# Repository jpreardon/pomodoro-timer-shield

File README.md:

Pomodoro Timer Shield for Arduino
=================================

This is a Pomodoro Timer, implemented  as an Arduino shield. The source code, schematic and board layout (in Eagle) are all included in this repository. For more information about the project, visit http://jpreardon.com/projects/pomodoro-timer/

© Copyright 2012-2019 John P. Reardon
Licensed under the MIT license.

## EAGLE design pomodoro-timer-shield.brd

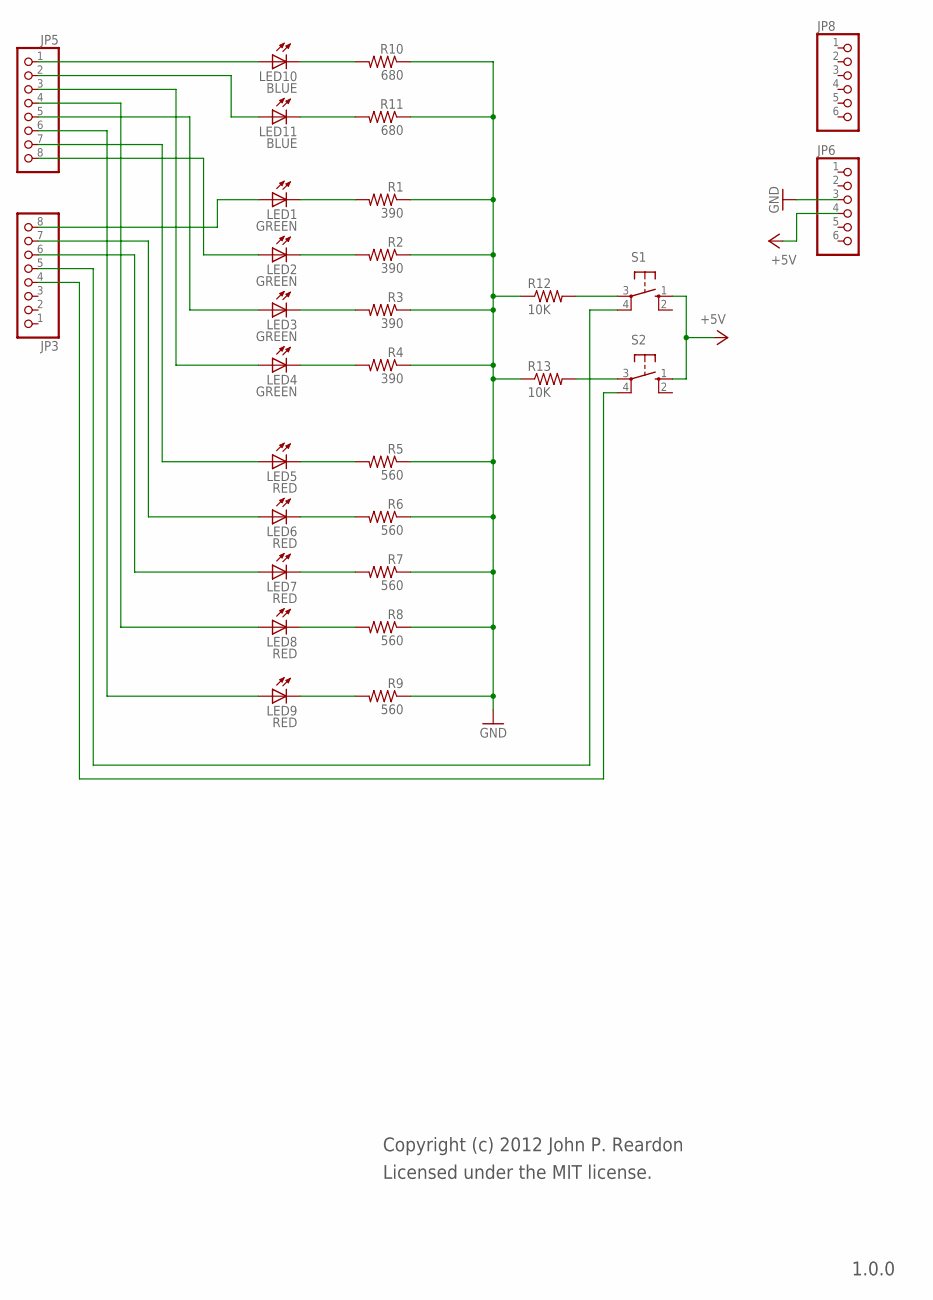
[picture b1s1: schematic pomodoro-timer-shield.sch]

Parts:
JP3, JP5: PINHD-1X8CLEANBIG; 1X08-CLEANBIG
JP6, JP8: PINHD-1X6CB; 1X06-CLEANBIG
LED1, LED2, LED3, LED4: GREEN; LED3MM
LED5, LED6, LED7, LED8, LED9: RED; LED3MM
LED10, LED11: BLUE; LED3MM
R1, R2, R3, R4: 390; 0204/7
R5, R6, R7, R8, R9: 560; 0204/7
R10, R11: 680; 0204/7
R12, R13: 10K; 0204/7
S1, S2: 10-XX; B3F-10XX

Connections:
+5V: JP6.4, S1.1 (S), S2.1 (S)
GND: JP6.3, R1.1, R2.1, R3.1, R4.1, R5.1, R6.1, R7.1, R8.1, R9.1, R10.1, R11.1, R12.1, R13.1
unnamed: JP5.1, LED10.A
unnamed: LED10.K (C), R10.2
unnamed: LED11.K (C), R11.2
unnamed: LED5.K (C), R5.2
unnamed: LED4.K (C), R4.2
unnamed: LED8.K (C), R8.2
unnamed: LED3.K (C), R3.2
unnamed: LED2.K (C), R2.2
unnamed: LED1.K (C), R1.2
unnamed: LED7.K (C), R7.2
unnamed: LED6.K (C), R6.2
unnamed: LED9.K (C), R9.2
unnamed: R12.2, S1.3
unnamed: R13.2, S2.3
unnamed: JP3.5, S1.4 (P1)
unnamed: JP3.4, S2.4 (P1)
unnamed: JP5.2, LED11.A
unnamed: JP3.8, LED1.A
unnamed: JP5.8, LED2.A
unnamed: JP5.7, LED5.A
unnamed: JP5.5, LED3.A
unnamed: JP5.3, LED4.A
unnamed: JP3.7, LED6.A
unnamed: JP3.6, LED7.A
unnamed: JP5.4, LED8.A
unnamed: JP5.6, LED9.A

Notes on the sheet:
Licensed under the MIT license.
1.0.0
Copyright (c) 2012 John P. Reardon

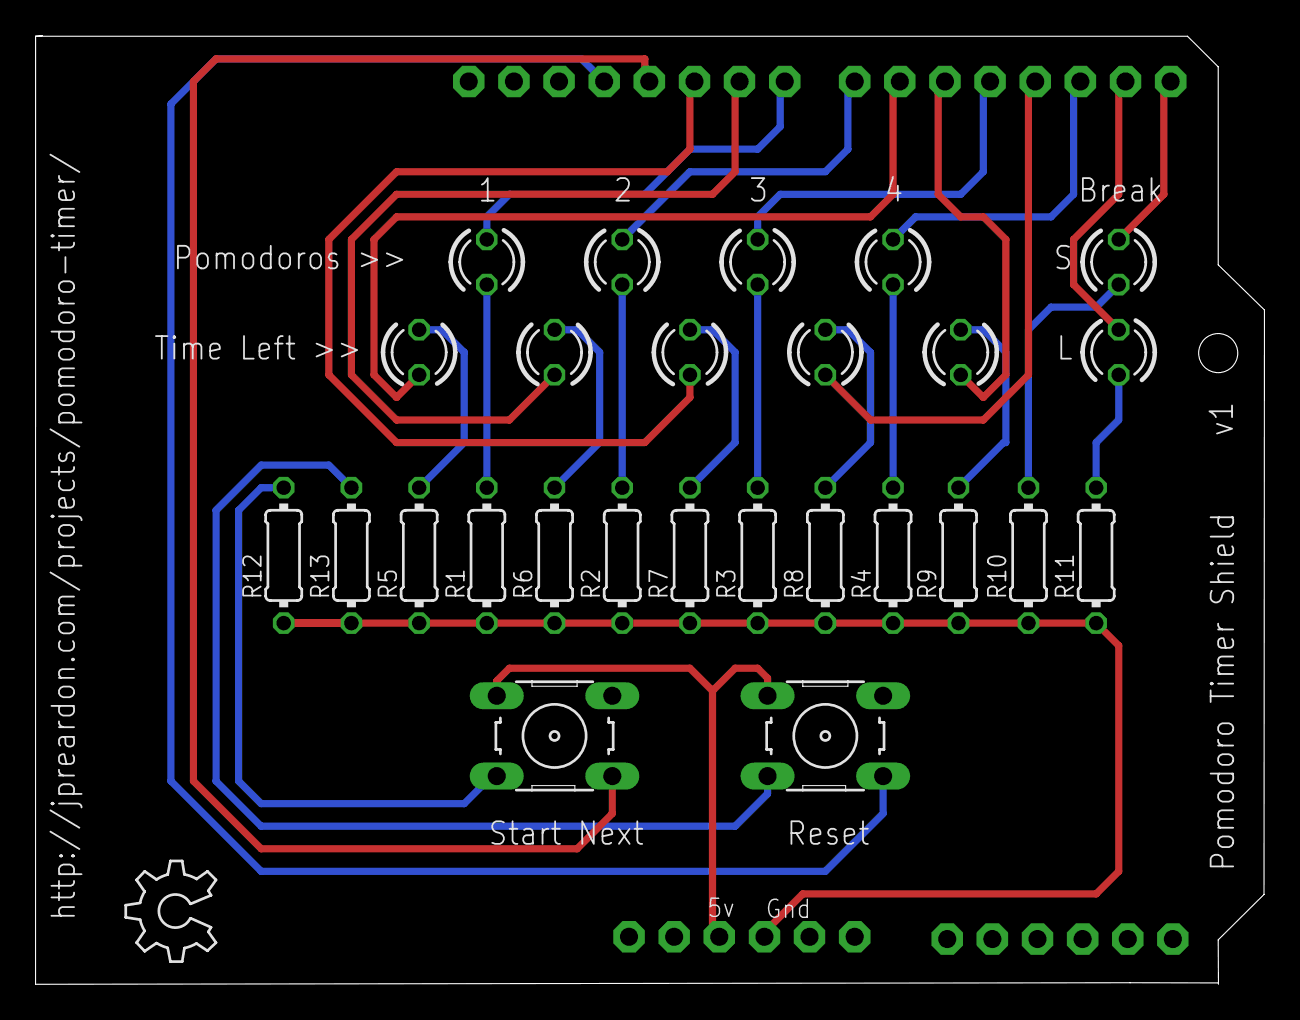
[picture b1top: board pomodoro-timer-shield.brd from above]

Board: 2 copper layers, 69.2 x 53.4 mm, 31 parts (0 on the bottom side), 28 nets.

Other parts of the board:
U$2: OSHW_6X200_NOTEXT

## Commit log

2012-12-28 Started working on the blinky, and timer functions
2012-12-28 Refactored some code into their own functions. This is mostly working now, enough for testing anyway.
2012-12-28 Fixed the timer LEDs light properly in relation to time left
2012-12-29 Fixed end-of-mode states
2012-12-31 Implemented fade instead of blink on for the timer LEDs
2013-01-01 Changed schematic for Arduino shield configuration
2013-01-29 Minor changes to the Arduino sketch (fade timing and comments), adding updated schematic, board layout and license. Updated readme
2019-01-17 Move pomodoro_timer.ino sketch to subfolder. Create .gitignore
2019-01-17 Dim the red lights a bit. Remove an unused function.
